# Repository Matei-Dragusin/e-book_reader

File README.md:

# README

## Diagrama bloc

---
## Bill Of Materials (BOM)
| Componentă                  | Procurare                                                                                                                                                                   | Datasheet                                               |
|-----------------------------|-----------------------------------------------------------------------------------------------------------------------------------------------------------------------------|---------------------------------------------------------|
| Button                      | [Mouser](https://ro.mouser.com/ProductDetail/CK/KMR221GULCLFS?qs=u2NJ%252B70r0goBXaNk7IrU0Q%3D%3D)                                                                          |[Datasheet](https://www.ckswitches.com/media/1479/kmr2.pdf)|
| Capacitor SUPERCAP          | [Mouser](https://ro.mouser.com/ProductDetail/Seiko-Semiconductors/CPH3225A?qs=3etwrb1wR%252BhUOph6lAO7eg%3D%3D)                                                             | [Datasheet](https://ro.mouser.com/datasheet/2/360/Seiko_Instruments_MicroBattery_E_20230330_2024Jan_-3561061.pdf)|
| Capacitor 100nF             | [Mouser](https://ro.mouser.com/ProductDetail/KEMET/C0402C104K4RAL?qs=pIZUS6sqCWCaMuP2QVR%2Fog%3D%3D)                                                                        | [Datasheet](https://ro.mouser.com/datasheet/2/447/KEM_C1018_X7R_SnPb_SMD-3316276.pdf)|
| Capacitor 4.7uF             | [Mouser](https://ro.mouser.com/ProductDetail/KEMET/C0402C475M9PAC7411?qs=cpo3%2FpBou2jRzZxyxJnMGg%3D%3D)                                                                    | [Datasheet](https://ro.mouser.com/datasheet/2/447/KEM_C1006_X5R_SMD-3316465.pdf)|
| Capacitor 100uF TANT        | [Mouser](https://ro.mouser.com/ProductDetail/KYOCERA-AVX/TAJW107M010RNJ?qs=Wtp%252Bf%2FAeVqIH8v1VxV%252B1Rg%3D%3D)                                                          | [Datasheet](https://ro.mouser.com/datasheet/2/40/TAJ-3165264.pdf)|
| Capacitor 4.7uF / 25V       | [Mouser](https://ro.mouser.com/ProductDetail/KYOCERA-AVX/12063C475KAZ2A?qs=%252BdQmOuGyFcG3LdbVp5waMw%3D%3D)                                                                | [Datasheet](https://ro.mouser.com/datasheet/2/40/X7RDielectric-2943470.pdf)|
| Capacitor 1uF               | [Mouser](https://ro.mouser.com/ProductDetail/KEMET/C0402C105K9PACTU?qs=UdQET6xYxVCMExqTDkuPeQ%3D%3D)                                                                        | [Datasheet](https://ro.mouser.com/datasheet/2/447/KEM_C1006_X5R_SMD-3316465.pdf)|
| Capacitor 10uF              | [Mouser](https://ro.mouser.com/ProductDetail/KEMET/C0402C106M9PACTU?qs=x4XeXhDQKnp%252Bz0lMlwMC3A%3D%3D)                                                                    | [Datasheet](https://ro.mouser.com/datasheet/2/447/KEM_C1006_X5R_SMD-3316465.pdf)|
| CHG_LED                     | [CPC](https://cpc.farnell.com/kingbright/kpg-1608zgc/led-smd-0603-grn/dp/SC20796)                                                                                           | [Datasheet](https://www.farnell.com/datasheets/2046349.pdf)|
| USBLC6-2SC6Y                | [Mouser](https://ro.mouser.com/ProductDetail/STMicroelectronics/USBLC6-2SC6Y?qs=gNDSiZmRJS%2FOgDexvXkdow%3D%3D)                                                             | [Datasheet](https://ro.mouser.com/datasheet/2/389/usblc6_2sc6y-1852505.pdf)|
| PGB1010603MR                | [Mouser](https://ro.mouser.com/ProductDetail/Littelfuse/PGB1010603MR?qs=gu7KAQ731URLg4GSnNNN7Q%3D%3D)                                                                       | [Datasheet](https://www.littelfuse.com/assetdocs/pulseguard-esd-suppressors-pgb1-datasheet?assetguid=8a337998-d54d-466b-be4e-dc5bcd1f9321)|
| SD0805S020S1R0              | [Mouser](https://ro.mouser.com/ProductDetail/KYOCERA-AVX/SD0805S020S1R0?qs=jCA%252BPfw4LHbpkAoSnwrdjw%3D%3D)                                                                | [Datasheet](https://ro.mouser.com/datasheet/2/40/schottky-3165252.pdf)|
| MBR0530                     | [Mouser](https://ro.mouser.com/ProductDetail/onsemi/MBR0530T3G?qs=3JMERSakebpEmdUS6GetdQ%3D%3D)                                                                             | [Datasheet](https://www.onsemi.com/products/discrete-power-modules/schottky-diodes-schottky-rectifiers/mbr0530t3g)|
| Capacitor 1uF / 50V         | [Mouser](https://ro.mouser.com/ProductDetail/TDK/C1608X7R1H105K080AB?qs=sGAEpiMZZMsh%252B1woXyUXjwVqLNpRsvnQGmKhuYn4DWE%3D)                                                 | [Datasheet](https://product.tdk.com/system/files/dam/doc/product/capacitor/ceramic/mlcc/catalog/mlcc_commercial_general_en.pdf)|
| Capacitor 0.1uF / 50V       | [Farnell](https://ro.farnell.com/multicomp-pro/mcmlr50v104kx7r/ceramic-capacitor-0-1uf-50v-x7r/dp/1600875?srsltid=AfmBOop-NuqSwaWYAsNDvdMnjraBeqfj0sl8f99iLZ_KJc8xpnT4fSqT) | [Datasheet](https://www.farnell.com/datasheets/2873577.pdf?_gl=1*x28a2*_gcl_au*MTYwODAzNzc2OC4xNzQzNDM1MjM4)|
| BD5229G-TR                  | [Mouser](https://ro.mouser.com/ProductDetail/ROHM-Semiconductor/BD5229G-TR?qs=4kLU8WoGk0vvnhrrYwdszw%3D%3D)                                                                 | [Datasheet](https://fscdn.rohm.com/en/products/databook/datasheet/ic/power/voltage_detector/bd52xxg-e.pdf)|
| XC6220A331MR-G              | [Mouser](https://ro.mouser.com/ProductDetail/Torex-Semiconductor/XC6220A331MR-G?qs=AsjdqWjXhJ8ZSWznL1J0gg%3D%3D)                                                            | [Datasheet](https://ro.mouser.com/datasheet/2/760/xc6220-3371556.pdf)|
| FH34SRJ-24S-0.5SH_99_       | [Mouser](https://ro.mouser.com/ProductDetail/Hirose-Connector/FH34SRJ-24S-0.5SH99?qs=vcbW%252B4%252BSTIpKBl5ap9J8Fw%3D%3D)                                                  | [Datasheet](https://ro.mouser.com/datasheet/2/185/FH34SRJ_24S_0_5SH_99__CL0580_1255_6_99_2DDrawing_0-1615044.pdf)|
| SAMACSYS_PARTS_USB4110-GF-A | [Mouser](https://ro.mouser.com/ProductDetail/GCT/USB4110-GF-A?qs=KUoIvG%2F9IlYiZvIXQjyJeA%3D%3D)                                                                            | [Datasheet](https://ro.mouser.com/datasheet/2/837/GCT_USB4110_Product_Drawing___20k_cycles-3455479.pdf)|
| QWIIC_RIGHT_ANGLEA          | [Mouser](https://ro.mouser.com/ProductDetail/JST-Commercial/SM04B-SRSS-TBLFSN?qs=cdbOS8ANM9B3FdyA6cNU2A%3D%3D)                                                              | [Datasheet](https://ro.mouser.com/datasheet/2/564/eSR_SZ-3476820.pdf)|
| 112A-TAAR-R03_ATTEND        | [LCSC](https://www.lcsc.com/product-detail/SD-Card-Connectors_Attend-Technology-112A-TAAR-R03_C6970445.html)                                                                | [Datasheet](https://www.lcsc.com/datasheet/lcsc_datasheet_2411220717_Attend-Technology-112A-TAAR-R03_C6970445.pdf)|
| Bobina                      | [Mouser](https://ro.mouser.com/ProductDetail/Wurth-Elektronik/744043680?qs=PGXP4M47uW6VkZq%252BkzjrHA%3D%3D)                                                                | [Datasheet](https://www.we-online.com/components/products/datasheet/744043680.pdf)|
| MCP73831                    | [Mouser](https://ro.mouser.com/ProductDetail/Microchip-Technology/MCP73831-2ACI-MC?qs=hH%252BOa0VZEiBneYTVdpuVdg%3D%3D)                                                     | [Datasheet](https://ro.mouser.com/datasheet/2/268/MCP73831_Family_Data_Sheet_DS20001984H-3441711.pdf)|
| PFMF.050.1                  | [Mouser](https://ro.mouser.com/ProductDetail/Schurter/PFMF.050.2?qs=1auRipcfynCums5v1iucSA%3D%3D)                                                                           | [Datasheet](https://ro.mouser.com/datasheet/2/358/typ_PFMF-1275918.pdf)|
| DMG2305UX-7                 | [Mouser](https://ro.mouser.com/ProductDetail/Diodes-Incorporated/DMG2305UX-7?qs=L1DZKBg7t5F%2FNBHrjfxC%252Bg%3D%3D)                                                         | [Datasheet](https://www.diodes.com/assets/Datasheets/DMG2305UX.pdf)|
| SI1308EDL-T1-GE3            | [Mouser](https://ro.mouser.com/ProductDetail/Vishay-Semiconductors/SI1308EDL-T1-GE3?qs=bX1%252BNvsK%2FBramh9tgpOaEw%3D%3D)                                                  | [Datasheet](https://www.vishay.com/docs/63399/si1308edl.pdf)|
| Resistor 10K                | [DigiKey](https://www.digikey.com/en/products/detail/venkel/CR0402-10W-102JT/12332774)                                                                                      | [Datasheet](https://data.venkel.com/documents/cr-series?_gl=1*mn27ew*_ga*MTAzMTIxOTYyMS4xNzQzNzU5MjAy*_ga_JRKGBZNVM8*MTc0Mzc1OTIwMS4xLjAuMTc0Mzc1OTIwMi41OS4wLjA.)|
| Resistor 100K               | [Venkel](https://venkel.com/part/CR0402-16W-1003FT)                                                                                                                         | [Datasheet](https://data.venkel.com/documents/cr-series?_gl=1*oleae1*_ga*MTAzMTIxOTYyMS4xNzQzNzU5MjAy*_ga_JRKGBZNVM8*MTc0Mzc1OTIwMS4xLjEuMTc0Mzc1OTM0My4zNi4wLjA.)|
| Resistor 5k1                | [Venkel](https://venkel.com/part/CR0402-10W-5101FT)                                                                                                                         | [Datasheet](https://data.venkel.com/documents/cr-series?_gl=1*1e041jc*_ga*MTAzMTIxOTYyMS4xNzQzNzU5MjAy*_ga_JRKGBZNVM8*MTc0Mzc1OTIwMS4xLjEuMTc0Mzc1OTU2Ny41MS4wLjA.)|
| Resistor 2k                 | [Venkel](https://www.venkel.com/part/CR0402-16W-2002FT)                                                                                                                     | [Datasheet](https://data.venkel.com/documents/cr-series?_gl=1*1sqolfs*_ga*MTAzMTIxOTYyMS4xNzQzNzU5MjAy*_ga_JRKGBZNVM8*MTc0Mzc1OTIwMS4xLjEuMTc0Mzc1OTY2OS4zNC4wLjA.)|
| Resistor 0.47               | [Mouser](https://ro.mouser.com/ProductDetail/Vishay-Beyschlag/MCT06030C4700FP500?qs=XsZ9OvPb0dt82KlzjdcMjQ%3D%3D)                                                           | [Datasheet](https://www.vishay.com/docs/28705/mcx0x0xpro.pdf)|
| BME688               | [Mouser](https://ro.mouser.com/ProductDetail/Bosch-Sensortec/BME688?qs=IS%252B4QmGtzzqQoVDscqwx3A%3D%3D)                                                           | [Datasheet](https://ro.mouser.com/datasheet/2/783/bst_bme688_fl000-2307034.pdf)|
| W25Q512JVEIQ               | [Mouser](https://ro.mouser.com/ProductDetail/Winbond/W25Q512JVEIQ?qs=l7cgNqFNU1jw6svr3at6tA%3D%3D)                                                           | [Datasheet](https://ro.mouser.com/datasheet/2/949/Winbond_W25Q512JV_Datasheet-3240039.pdf)|
| ESP32-C6-WROOM-1-N8               | [Mouser](https://ro.mouser.com/ProductDetail/Espressif-Systems/ESP32-C6-WROOM-1-N8?qs=8Wlm6%252BaMh8ST02Gmwp74cw%3D%3D)                                                           | [Datasheet](https://ro.mouser.com/datasheet/2/891/Espressif_ESP32_C6_WROOM_1__Datasheet_V0_1_PRELIMI-3239987.pdf)|
| DS3231SN#               | [Mouser](https://ro.mouser.com/ProductDetail/Analog-Devices-Maxim-Integrated/DS3231SN?qs=1eQvB6Dk1vhUlr8%2FOrV0Fw%3D%3D)                                                           | [Datasheet](https://ro.mouser.com/datasheet/2/609/DS3231-3421123.pdf)|
| MAX17048G+T10               | [Mouser](https://ro.mouser.com/ProductDetail/Analog-Devices-Maxim-Integrated/MAX17048G%2bT10?qs=D7PJwyCwLAoGnnn8jEPRBQ%3D%3D)                                                           | [Datasheet](https://ro.mouser.com/datasheet/2/609/MAX17048_MAX17049-3469099.pdf)|
---
# Functionalitatea Hardware

**Sursa de Alimentare si Energie:**
- **USB cu ESD:** Protectie la alimentare si transfer de date.
- **Circuit de Incarcare Li-Po - MCP73831:** Managementul controlat al incarcarii pentru acumulatorul de 1800 mAh.
- **Baterie Li-Po & LDO Voltage Regulator:** Stabilizeaza tensiunea la 3.3V pentru componentele sistemului.

**Microcontroller & Interfete:**
- **ESP32-C6:**
    - **SPI:** Interconecteaza memoria NOR Flash, cardul SD și displayul e-paper.
    - **I2C:** Faciliteaza comunicarea cu RTC DS3231, senzorul BME688 și modulele aditionale.
    - **UART:** Dedicat pentru debugging și comunicatii seriale.
    - **GPIO:** Utilizat pentru butoane si puncte de testare.

**Module de Stocare & Afisare:**
- **Memorie NOR Flash (SPI):** Stocare eficienta pentru firmware si date operationale.
- **Card SD (SPI):** Ofera capacitate de stocare suplimentara.
- **E-Paper Display:** Asigura vizualizari precise cu consum energetic minim, operat prin SPI.

**Module Suplimentare & Senzori:**
- **RTC DS3231 (I2C):** Furnizeaza timpul real sistemului.
- **Senzor BME688 (I2C):** Monitorizeaza temperatura, umiditatea, presiunea si calitatea aerului.
- **Conector Qwiic/Stemma QT (I2C):** Faciliteaza integrarea modulelor aditionale.
- **Test Pads & Butoane (GPIO):** Suporta diagnosticarea si interactiunea directa.

**Optimizare Energetica:**
- **Mod Low-Power al ESP32-C6:** Optimizeaza consumul prin ajustarea dinamica a frecventei si ciclurilor active.
- **Stabilitate prin LDO:** Garanteaza o tensiune stabila de 3.3V.
- **Componente SMD (ex: capsula 0402):** Reduce consumul energetic prin dimensiuni compacte si eficienta ridicata.

---

# ESP32-C6 Pin Mapping

| Nume | GPIO        | Utilizare                                      | Observații                                                                                                                      |
|------|-------------|------------------------------------------------|---------------------------------------------------------------------------------------------------------------------------------|
| 3V3  | 3V3         | Alimentare 3.3V                                | Sursa de tensiune pentru ESP32-C6 și componente logice.                                                                         |
| SCK (SPI) | IO6         | Clock pentru SPI                               | Asigură semnalul de ceas pentru transferuri rapide.                                                                             |
| MOSI (SPI) | IO7         | Transmitere date SPI                           | Trimite date către NOR Flash, SD Card și E-Paper.                                                                               |
| MISO (SPI) | IO2         | Recepție date SPI                              | Primește date de la dispozitivele SPI.                                                                                          |
| FLASH_CS | IO11        | Selectare SPI pentru NOR Flash                 | Selectează memoria NOR Flash pe magistrala SPI.                                                                                 |
| EPD_CS | IO10        | Selectare SPI pentru E-Paper                   | Selectează afișajul e-paper.                                                                                                    |
| SDA (I2C) | IO21        | Linie de date I2C                              | Conectează RTC DS3231, senzorul BME688 și conectorul Qwiic/Stemma QT.                                                           |
| SCL (I2C) | IO22        | Linie de ceas I2C                              | Sincronizează comunicația I2C.                                                                                                  |
| TX (UART) | TXD0/GPIO16 | Transmitere date UART                          | Utilizat pentru debug și comunicații seriale.                                                                                   |
| RX (UART) | RXD0/GPIO17 | Recepție date UART                             | Utilizat pentru debug și comunicații seriale.                                                                                   |
| Buton Reset | EN          | Resetare ESP32-C6                              | Pin dedicat pentru resetul sistemului.                                                                                          |
| Buton Boot | IO9         | Intrare în bootloader                          | Pin dedicat pentru a intra în modul boot.                                                                                       |
| Buton Change | IO15        | Schimbare mod operare                          | Permite comutarea între modurile de funcționare.                                                                                |
| EPD DC | IO5         | Data/Command pentru E-Paper                    | Disting între semnal de comandă și semnal de date pentru afișaj.                                                                |
| EPD RST | IO23        | Resetare E-Paper                               | Resetează afișajul e-paper când este necesar.                                                                                   |
| EPD BUSY | IO3         | Indicator stare E-Paper                        | Semnal care indică dacă afișajul este ocupat.                                                                                   |
| INT_RTC | IO0         | Semnal de întrerupere de la RTC (DS3231)        | Activează microcontrolerul.                                                                                                     |
| 32KHZ | IO1         | Semnal de ceas 32 kHz                 | Linie de oscilație pentru DS3231 sau alt modul (nu intră direct în ESP).                                                        |
| SS_SD| IO4         | Chip Select pentru card SD (SPI)                | Selectează cardul SD pe magistrala SPI.                                                                                         |
| USB_D- | IO12        | Linie diferențială USB (minus)                  | Conexiune la portul USB.                                                                                                        |
| USB_D+ | IO13        | Linie diferențială USB (plus)                   | Conexiune la portul USB.                                                                                                        |
| RTC_RST | IO18        | Reset extern/semnal RTC                         | Folosit pentru a reseta ceasul de timp real                                                                                     |
| I2C_PW | IO19        | Linia de alimentare / enable pentru I2C         | Activează/dezactivează alimentarea senzorilor I2C pentru economisirea energiei.                                                 |
| EPD_3V3_C | IO20        | Linie de alimentare 3.3V pentru E-Paper         | Această linie furnizează 3.3V specifice afișajului e-paper, separate de alimentarea principală, pentru stabilitatea semnalelor. |

---
## Motivatie

- **SPI** (SCK, MOSI, MISO, CS-uri) asigura transferul accelerat pentru memoria externa (Flash), cardul SD si ecranul e-paper.
- **I2C** (SDA, SCL) integreaza senzorii (RTC, BME688) si conectorul Qwiic, permitand utilizarea comuna a magistralei cu impact redus asupra consumului energetic.
- **UART** (TX, RX) este implementat pentru scopuri de debugging.
- **GPIO suplimentare** (butoane, test pads) ofera suport pentru controlul manual si procesele de diagnosticare.

---

## Pasii de Implementare

- **Schematic:** Am proiectat schematicul in concordanta cu specificatiile proiectului.
- **Redesenarea PCB-ului:** Am reconstruit placa PCB și am aranjat componentele conform referintei de design.
- **Autorutare:** Am implementat autorutarea pe ambele fete, cu grosimea traseelor de semnal de 0.15mm.
- **Net Class pentru Putere:** Am organizat traseele de alimentare intr-un netclass dedicat, le-am evidential cromatic si le-am dimensionat manual la 0.3mm pentru o distributie optima a energiei.
- **Planuri de Masă si Via Stitching:** Am implementat planurile de masă pe ambele fete si am aplicat via stitching in proximitatea modulului ESP pentru conexiuni eficiente intre straturi.
- **Modele 3D:** Am procurat modelele 3D ale componentelor de pe [ComponentSearchEngine](https://componentsearchengine.com/), le-am incorporat în Fusion 360 si le-am plasat adecvat pe PCB.
- **Integrarea in Carcasa:** Am incorporat placa in carcasa si am adaptat designul carcasei pentru a acomoda butoanele si conectorii.
- **Modelele 3D pentru Baterie si Display:** Am dezvoltat reprezentarile 3D pentru baterie si display, conectand conductorii la punctele de test corespunzatoare si asigurand pozitionarea optima in carcasa.
- **Export:** In etapa finala, am generat documentatia necesara - fisiere Gerber, Pick and Place (CPL) si BOM, pregatindu-le pentru procesul de fabricatie.

---

## Probleme Intampinate si Decizii de Acceptare a Erorilor

- **Erori SMD-Hole Board Outline Clearance la Mufa USB:**  
  Am identificat doua erori de tip SMD-Hole Board Outline Clearance asociate mufei USB. Aceste erori au fost considerate acceptabile conform indicatiilor tehnice primite.

---

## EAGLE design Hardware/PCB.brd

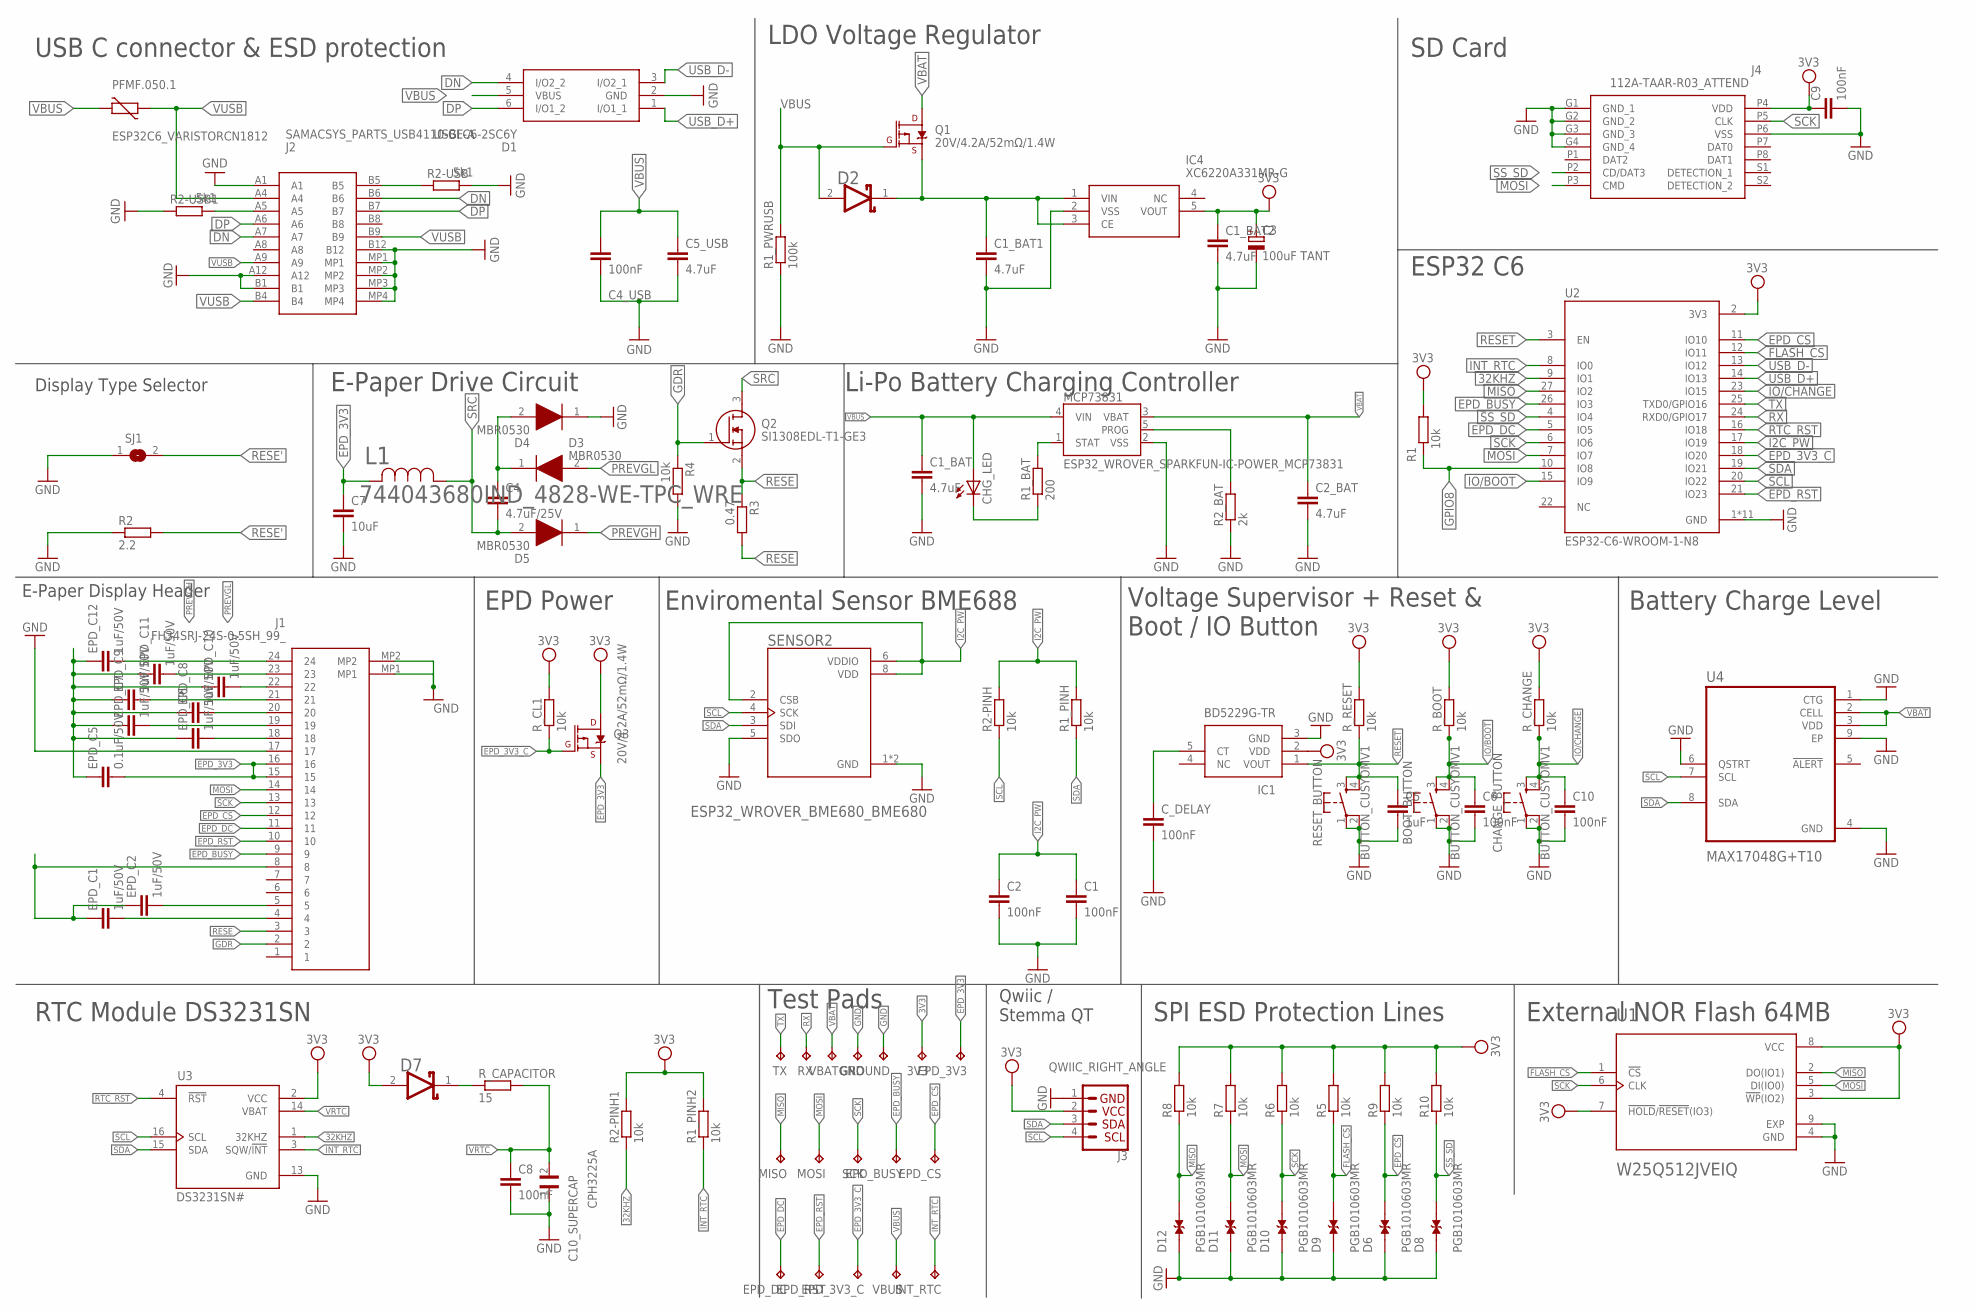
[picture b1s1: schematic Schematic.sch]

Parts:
3V3: TPTP20R; TP20R
BOOT_BUTTON: BUTTON_CUSYOMV1; MYBUTTON
C1, C2, C4_USB, C6, C8, C9, C10: 100nF; EAGLE-LTSPICE_C0402
C1_BAT, C1_BAT1, C1_BAT2, C2_BAT, C5_USB: 4.7uF; EAGLE-LTSPICE_C0402
C3: 100uF TANT; RCL_CT3528
C4: 4.7uF/25V; EAGLE-LTSPICE_C0402
C5: 1uF; EAGLE-LTSPICE_C0402
C7: 10uF; EAGLE-LTSPICE_C0402
C10_SUPERCAP: CPH3225A; CAPCP3225X100N
CHANGE_BUTTON: BUTTON_CUSYOMV1; MYBUTTON
CHG_LED: ADAFRUIT_LEDCHIP-LED0603; ADAFRUIT_CHIP-LED0603
C_DELAY: 100nF; EAGLE-LTSPICE_C0402
D1: USBLC6-2SC6Y; SOT95P280X145-6N
D2, D7: ESP32_WROVER_AVX---SD0805S020S1R0_AVX_SD0805S020S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; ESP32_WROVER_AVX---SD0805S020S1R0_AVX_SD0805S020S1R0_0
D3, D4, D5: MBR0530; SOD3716X135N
D6, D8, D9, D10, D11, D12: PGB1010603MR; DIOC1608X36N
EPD_3V3, EPD_3V3_C: TPTP20R; TP20R
EPD_BUSY: TPTP20R; TP20R
EPD_C1, EPD_C2, EPD_C6, EPD_C7, EPD_C8, EPD_C9, EPD_C10, EPD_C11, EPD_C12: 1uF/50V; EAGLE-LTSPICE_C0402
EPD_C5: 0.1uF/50V; EAGLE-LTSPICE_C0402
EPD_CS: TPTP20R; TP20R
EPD_DC: TPTP20R; TP20R
EPD_RST: TPTP20R; TP20R
GND: TPTP20R; TP20R
GROUND: TPTP20R; TP20R
IC1: BD5229G-TR; SOT95P280X125-5N
IC4: XC6220A331MR-G; SOT95P280X120-5N
INT_RTC: TPTP20R; TP20R
J1: FH34SRJ-24S-0.5SH_99_; FH34SRJ24S05SH99
J2: SAMACSYS_PARTS_USB4110-GF-A; SAMACSYS_PARTS_USB4110GFA
J3: QWIIC_RIGHT_ANGLE; JST04_1MM_RA
J4: 112A-TAAR-R03_ATTEND; 112ATAARR03ATTEND
L1: 744043680IND_4828-WE-TPC_WRE; IND_4828-WE-TPC_WRE
MCP73831: ESP32_WROVER_SPARKFUN-IC-POWER_MCP73831; ESP32_WROVER_SPARKFUN-IC-POWER_SOT23-5
MISO: TPTP20R; TP20R
MOSI: TPTP20R; TP20R
PFMF.050.1: ESP32C6_VARISTORCN1812; ESP32C6_VARISTOR_CT/CN1812
Q1, Q3: 20V/4.2A/52mΩ/1.4W; ESP32_WROVER_SPARKFUN-DISCRETESEMI_SOT23-3
Q2: SI1308EDL-T1-GE3; ESP32_WROVER_SPARKFUN-DISCRETESEMI_SOT23-3
R1, R1_PINH, R1_PINH2, R2-PINH, R2-PINH1, R4, R5, R6, R7, R8, R9, R10: 10k; ESP32_WROVER_EAGLE-LTSPICE_R0402
R1_BAT: 200; ESP32_WROVER_EAGLE-LTSPICE_R0402
R1_PWRUSB: 100k; ESP32_WROVER_EAGLE-LTSPICE_R0402
R2: 2.2; ESP32_WROVER_EAGLE-LTSPICE_R0402
R2-USB, R2-USB1: 5k1; ESP32_WROVER_EAGLE-LTSPICE_R0402
R2_BAT: 2k; ESP32_WROVER_EAGLE-LTSPICE_R0402
R3: 0.47; ESP32_WROVER_EAGLE-LTSPICE_R0402
RESET_BUTTON: BUTTON_CUSYOMV1; MYBUTTON
RX: TPTP20R; TP20R
R_BOOT: 10k; ESP32_WROVER_EAGLE-LTSPICE_R0402
R_CAPACITOR: 15; ESP32_WROVER_EAGLE-LTSPICE_R0402
R_CHANGE: 10k; ESP32_WROVER_EAGLE-LTSPICE_R0402
R_CL1: 10k; ESP32_WROVER_EAGLE-LTSPICE_R0402
R_RESET: 10k; ESP32_WROVER_EAGLE-LTSPICE_R0402
SCK: TPTP20R; TP20R
SENSOR2: ESP32_WROVER_BME680_BME680; ESP32_WROVER_BME680_PSON80P300X300X100-8N
SJ1: SJ
TX: TPTP20R; TP20R
U1: W25Q512JVEIQ; SON127P600X800X80-9N
U2: ESP32-C6-WROOM-1-N8; XCVR_ESP32-C6-WROOM-1-N8
U3: DS3231SN#; SOIC127P1032X265-16N
U4: MAX17048G+T10; SON50P200X200X80-9N
VBAT: TPTP20R; TP20R
VBUS: TPTP20R; TP20R

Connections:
3V3: 3V3.TP, C1_BAT2.1, C3.+, C9.1, D7.2 (ANODE), IC1.2 (VDD), IC4.5 (VOUT), J3.2, J4.P4 (VDD), Q3.3 (D), R1.2, R1_PINH2.2, R2-PINH1.2, R5.2, R6.2, R7.2, R8.2, R9.2, R10.2, R_BOOT.2, R_CHANGE.2, R_CL1.2, R_RESET.2, U1.3 (!WP!(IO2)), U1.7 (!HOLD!/!RESET!(IO3)), U1.8 (VCC), U2.2 (3V3), U3.2 (VCC)
32KHZ: R2-PINH1.1, U2.9 (IO1), U3.1 (32KHZ)
DN: D1.4 (I/O2_2), J2.A7, J2.B6
DP: D1.6 (I/O1_2), J2.A6, J2.B7
EPD_3V3: C7.1, EPD_3V3.TP, EPD_C5.2, J1.15, J1.16, L1.2, Q3.2 (S)
EPD_3V3_C: EPD_3V3_C.TP, Q3.1 (G), R_CL1.1, U2.18 (IO20)
EPD_BUSY: EPD_BUSY.TP, J1.9, U2.26 (IO3)
EPD_CS: D6.2, EPD_CS.TP, J1.12, R9.1, U2.11 (IO10)
EPD_DC: EPD_DC.TP, J1.11, U2.5 (IO5)
EPD_RST: EPD_RST.TP, J1.10, U2.21 (IO23)
FLASH_CS: D9.2, R5.1, U1.1 (!CS), U2.12 (IO11)
GDR: J1.2, Q2.1 (G), R4.1
GND: BOOT_BUTTON.1, BOOT_BUTTON.2, C1.2, C1_BAT.2, C1_BAT1.2, C1_BAT2.2, C2.2, C2_BAT.2, C3.-, C4_USB.2, C5.2, C5_USB.2, C6.2, C7.2, C8.2, C9.2, C10.2, C10_SUPERCAP.1, CHANGE_BUTTON.1, CHANGE_BUTTON.2, C_DELAY.2, D1.2 (GND), D4.1 (K), D6.1, D8.1, D9.1, D10.1, D11.1, D12.1, GND.TP, GROUND.TP, IC1.3 (GND), IC4.2 (VSS), J1.17, J1.MP1, J1.MP2, J2.A1, J2.A12, J2.B1, J2.B12, J2.MP1, J2.MP2, J2.MP3, J2.MP4, J3.1, J4.G1 (GND_1), J4.G2 (GND_2), J4.G3 (GND_3), J4.G4 (GND_4), J4.P6 (VSS), MCP73831.2 (VSS), R1_PWRUSB.1, R2.1, R2-USB.2, R2-USB1.1, R2_BAT.1, R4.2, RESET_BUTTON.1, RESET_BUTTON.2, SENSOR2.1 (GND), SENSOR2.5 (SDO), SENSOR2.7 (GND), SJ1.1, U1.4 (GND), U1.9 (EXP), U2.1 (GND), U2.28 (GND), U2.29_1 (GND), U2.29_2 (GND), U2.29_3 (GND), U2.29_4 (GND), U2.29_5 (GND), U2.29_6 (GND), U2.29_7 (GND), U2.29_8 (GND), U2.29_9 (GND), U3.13 (GND), U4.1 (CTG), U4.4 (GND), U4.6 (QSTRT), U4.9 (EP)
GPIO8: R1.1, U2.10 (IO8)
I2C_PW: C1.1, C2.1, R1_PINH.2, R2-PINH.2, SENSOR2.2 (CSB), SENSOR2.6 (VDDIO), SENSOR2.8 (VDD), U2.17 (IO19)
INT_RTC: INT_RTC.TP, R1_PINH2.1, U2.8 (IO0), U3.3 (SQW/!INT)
IO/BOOT: BOOT_BUTTON.3, BOOT_BUTTON.4, C6.1, U2.15 (IO9)
IO/CHANGE: C10.1, CHANGE_BUTTON.3, CHANGE_BUTTON.4, U2.23 (IO15)
MISO: D12.2, MISO.TP, R8.1, U1.2 (DO(IO1)), U2.27 (IO2)
MOSI: D11.2, J1.14, J4.P3 (CMD), MOSI.TP, R7.1, U1.5 (DI(IO0)), U2.7 (IO7)
unnamed: J2.A5, R2-USB1.2
unnamed: J2.B5, R2-USB.1
unnamed: C1_BAT1.1, D2.1 (CATHODE), IC4.1 (VIN), IC4.3 (CE), Q1.2 (S)
unnamed: EPD_C2.2, J1.5
unnamed: EPD_C5.1, EPD_C6.1, EPD_C7.1, EPD_C8.1, EPD_C9.1, EPD_C10.1, EPD_C11.1, EPD_C12.1
unnamed: C_DELAY.1, IC1.5 (CT)
unnamed: C4.1, D3.1 (K), D4.2 (A)
unnamed: CHG_LED.C, R1_BAT.1
unnamed: MCP73831.1 (STAT), R1_BAT.2
unnamed: EPD_C12.2, J1.24
unnamed: MCP73831.5 (PROG), R2_BAT.2
unnamed: D7.1 (CATHODE), R_CAPACITOR.1
unnamed: EPD_C10.2, J1.22
unnamed: EPD_C8.2, J1.20
unnamed: EPD_C7.2, J1.19
unnamed: EPD_C6.2, J1.18
unnamed: EPD_C1.1, EPD_C2.1, J1.8
unnamed: EPD_C1.2, J1.4
PREVGH: D5.1 (K), EPD_C9.2, J1.21
PREVGL: D3.2 (A), EPD_C11.2, J1.23
RESE: J1.3, Q2.2 (S), R3.1
RESE': R2.2, SJ1.2
RESET: C5.1, IC1.1 (VOUT), RESET_BUTTON.3, RESET_BUTTON.4, R_RESET.1, U2.3 (EN)
RESET1: R_CHANGE.1
RESET2: R_BOOT.1
RTC_RST: U2.16 (IO18), U3.4 (!RST)
RX: RX.TP, U2.24 (RXD0/GPIO17)
SCK: D10.2, J1.13, J4.P5 (CLK), R6.1, SCK.TP, U1.6 (CLK), U2.6 (IO6)
SCL: J3.4, R2-PINH.1, SENSOR2.4 (SCK), U2.20 (IO22), U3.16 (SCL), U4.7 (SCL)
SDA: J3.3, R1_PINH.1, SENSOR2.3 (SDI), U2.19 (IO21), U3.15 (SDA), U4.8 (SDA)
SRC: C4.2, D5.2 (A), L1.1, Q2.3 (D)
SS_SD: D8.2, J4.P2 (CD/DAT3), R10.1, U2.4 (IO4)
TX: TX.TP, U2.25 (TXD0/GPIO16)
USB_D+: D1.1 (I/O1_1), U2.14 (IO13)
USB_D-: D1.3 (I/O2_1), U2.13 (IO12)
VBAT: C2_BAT.1, MCP73831.3 (VBAT), Q1.3 (D), U4.2 (CELL), U4.3 (VDD), VBAT.TP
VBUS: C1_BAT.1, C4_USB.1, C5_USB.1, CHG_LED.A, D1.5 (VBUS), D2.2 (ANODE), MCP73831.4 (VIN), Q1.1 (G), R1_PWRUSB.2, VBUS.TP
VRTC: C8.1, C10_SUPERCAP.2, R_CAPACITOR.2, U3.14 (VBAT)
VUSB: J2.A4, J2.A9, J2.B4, J2.B9, PFMF.050.1.1

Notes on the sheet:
Display Type Selector
E-Paper Display Header
USB C connector & ESD protection
LDO Voltage Regulator
SD Card
E-Paper Drive Circuit
Li-Po Battery Charging Controller
ESP32 C6
EPD Power
Enviromental Sensor BME688
Voltage Supervisor + Reset & Boot / IO Button
Battery Charge Level
RTC Module DS3231SN
Test Pads
Qwiic / Stemma QT
External NOR Flash 64MB
SPI ESD Protection Lines

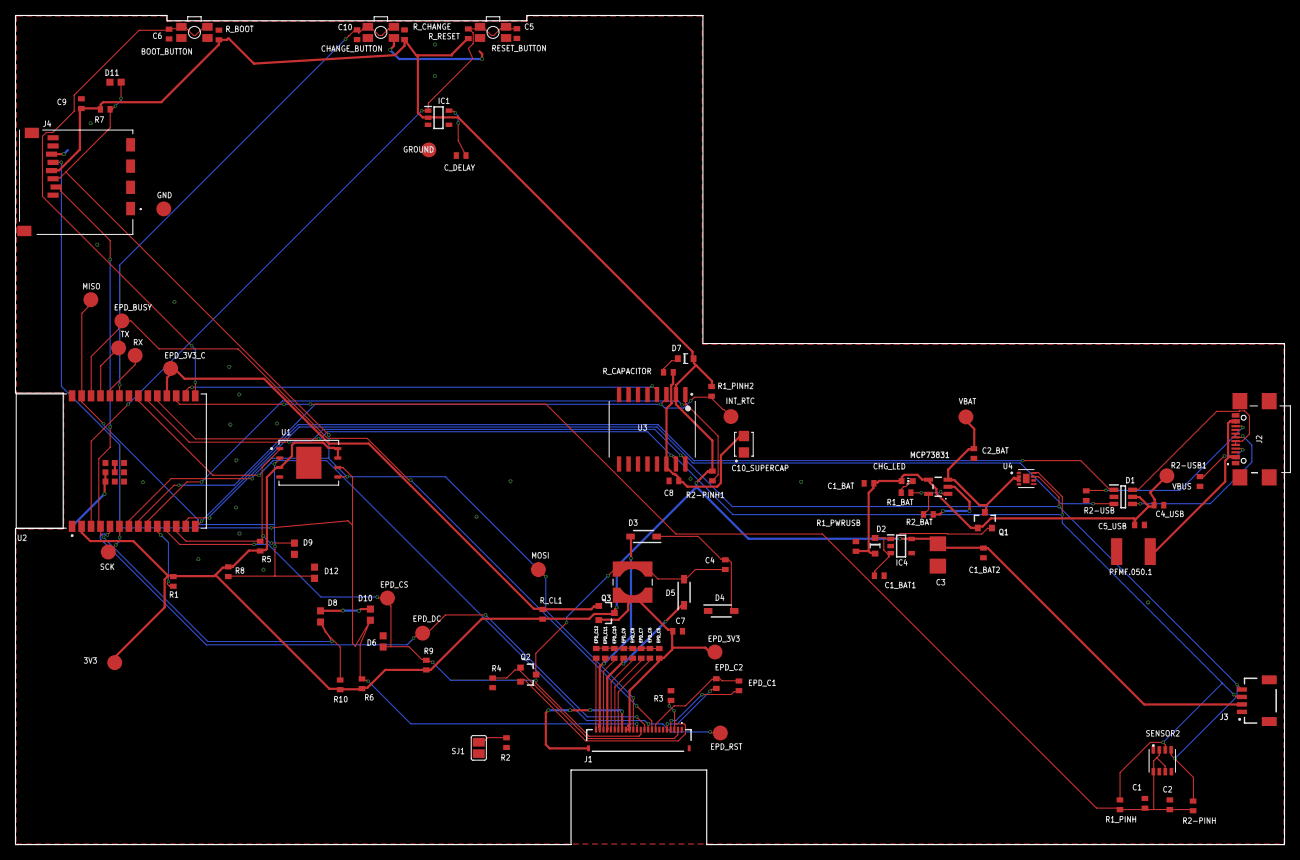
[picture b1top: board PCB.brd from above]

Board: 2 copper layers, 170.2 x 111.2 mm, 103 parts (0 on the bottom side), 57 nets.

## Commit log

2025-04-05 Update Images
2025-04-05 Add f3d and update pick&place
2025-04-05 Added diagram & update readme
2025-04-05 Update LICENSE
2025-04-14 Final version
    Updated files to solve #1 #2 #3 #4 #5.
2025-04-14 Updated images

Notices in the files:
parts and their libraries:
COPYRIGHT: Copyright (C) 2024 Ultra Librarian. All rights reserved.
